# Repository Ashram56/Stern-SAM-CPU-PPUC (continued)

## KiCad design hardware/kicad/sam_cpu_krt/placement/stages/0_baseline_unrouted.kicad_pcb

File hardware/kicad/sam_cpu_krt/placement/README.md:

# SAM CPU PPUC: optimized placement, then KRT routing (run C)

The placement plan applied to the KiCadRoutingTools experiment: measure the baseline, write placement constraints,
generate placement candidates scored on ratsnest length and crossings, keep the best two, route them on a copper-free
copy with KRT, pour the zones, and grade with the JLCPCB 4-layer rules. `../` (run A) is left as it was.

`sam_cpu.kicad_pcb` here is the result: the widened candidate, routed and with zones refilled.

Red F.Cu, blue B.Cu, green In1.Cu, yellow In2.Cu; pours hidden.

## Result

Graded by `kicad-cli pcb drc --refill-zones` (KiCad 10.0.6) with `sam_cpu.kicad_dru` (copied from
`/mnt/project-files/hardware/jlcpcb_rules/`) and the JLCPCB board minimums in `sam_cpu.kicad_pro`.

| | Freerouting (0ca768b) | KRT run A (`../`) | **KRT run C (this folder)** |
|---|---|---|---|
| Placement | as drawn | as drawn | widened board, optimized |
| Unconnected items | 37 | 6 | **2**: `GI_PWM` and the Pi's two 3V3 pins (see below) |
| Clearance / short / crossing | 0 | 0 | 0 |
| Hole to hole, different nets (JLC 0.5 mm) | 5 | 0 | 0 |
| Copper to edge (JLC 0.3 mm) | 0 | 0 | 0 |
| Starved thermal reliefs | — | 21 | 15 |
| Dangling track / via stubs | — | 7 | 6 tracks, 0 vias |
| Signal track at 0.1 mm | — | 2693 mm | **0** (`--escalation off`) |
| Tracks / vias | — | 7298 / 1282 | 6033 / 1147 |
| Track length F / In1 / In2 / B (mm) | — | 7907 / 2025 / 1912 / 6796 | 8005 / 1522 / 1479 / 6150 |
| Non-isolated copper in the GND_ISO area | — | none | none |

The remaining DRC items (199 silk overlap, 120 silk over copper, 199 library, 5 silk to edge, 4 mounting holes over
6.3 mm, 4 PTH rings) are the same as on the other boards and are not routing issues. Report: `drc/drc_widened_final.rpt`.

Still open:

- `GI_PWM` (U4 to the R185 area near U15): the end at (97.8, 119.95) is boxed in by neighbouring tracks. Three passes,
  including one allowed to rip the blocking nets, did not close it. It is one short track to add by hand.
- `PI_3V3`: the Pi header's two 3V3 pins (1 and 17). The schematic had them on a no-connect flag; they are now a
  named net (`PI_3V3` label plus a PWR_FLAG, since the Pi drives it) and need one short track between the two pins.

Power tracks still under their class width (requested width not reached in a tight spot; no track went below 0.2 mm):
`Net-(JP1-B)` 26.6 mm at 0.2 instead of 0.8, `Net-(D1-A1)` 12.7 mm at 0.2 instead of 0.8, `+12V` 3.6 mm at 0.4,
`+5V` 5.2 mm at 0.2, `+3V3` 35.8 mm and `+1V1` 12.4 mm at 0.2 instead of 0.25. The JP1-B and D1-A1 sections should
be widened by hand (`scripts/power_widths.py`).

## Placement metrics

Ratsnest = sum of per-net minimum spanning trees over pad centres, without GND, +3V3 and GND_ISO (planes);
crossings = ratsnest segments crossing each other (`scripts/ratsnest.py`).

| Candidate | Ratsnest (mm) | Crossings | Notes |
|---|---|---|---|
| baseline (Freerouting 0ca768b placement) | 14534 | 3391 | |
| c1: U6/U7 swap with their caps | 14514 | 3438 | 1 courtyard overlap, dropped |
| c2: optimizer, 3 mm max move | 14052 | 2389 | |
| c3: swap + 3 mm | 14007 | 2482 | |
| c4k: swap + 6 mm, decap groups, heatsink keep-out | 13642 | 1928 | routed: 286/304 first pass |
| **c5k: widened board + swap + 10 mm, decap groups, heatsink keep-out** | **13391** | **1391** | routed: 297/304 first pass |

Both kept candidates have no courtyard or clearance overlaps, nothing in the heatsink area (x 89-137, y 71-84) and no tall
parts under the Pi. The optimizer scatters and rotates passives more than a hand layout would
(`placement_before_after.png`, baseline left, widened right); a tidy-up pass for assembly and silkscreen is still needed.

**The widened board.** The top-right part of the board was extended by 21.35 mm to x 172 (KiCad coordinates), from the
top edge down to y 126.5, where a notch keeps the Pi's overhang free. The right-edge connectors J17, J22, J23, J24 and
J30 moved right with the edge by 21.35 mm; no mounting hole moved. Check that the harness reaches the new connector
positions before keeping this.

Locked parts (`locks.txt`, `placement_constraints.yaml`): all connectors, mounting holes, SW1-3, BT1, JP1, U23/U24
(heatsink), the isolated RS485 parts and U4 with its regulator parts.

## Routing

The original-size candidate ended with 8 nets open after its clean-up pass, so only the widened one was finished.

1. `scripts/route_chain.sh`: refill zones, fan out U4 with `qfn_fanout.py`, route the isolated nets, add a keep-out
   on User.2 around GND_ISO (outline + 2 mm), then route everything else. Layer costs 1/3/3/1, grid 0.1 mm,
   `--escalation off` (no narrowing), `--hole-to-hole-clearance 0.5`. Widened board: 79 min.
2. `scripts/route_cleanup.sh`: open nets plus GND at 0.05 mm grid (13 min), then the last two nets (3 min).
3. GND pad taps: the outer GND pours were removed from a copy, GND routed so every GND pad gets its own via into the
   In1 plane, and the pours put back. This closed the last 20 GND pads the pours did not reach.
4. `kicad-cli pcb drc --refill-zones --save-board` with the JLC rules.

Stage files: `stages/0_baseline_unrouted.kicad_pcb` (copper stripped), `stages/1_placed_widened.kicad_pcb` and
`stages/1_placed_original_size.kicad_pcb` (optimized, unrouted). Placement commands (KRT `py_placer/place_optimize.py`):

```
place_optimize.py c5_wide.kicad_pcb c5k.kicad_pcb --max-displacement 10 --ignore-nets GND +3V3 GND_ISO \
  --lock $(cat locks.txt) --group-by decap --intent intent.json
```

`c5_wide` is the baseline with U6/U7 swapped (`scripts/move.py`), the outline and zones widened (`scripts/widen.py`)
and the right-edge connectors moved. `c4k` uses `--max-displacement 6` on the original outline.

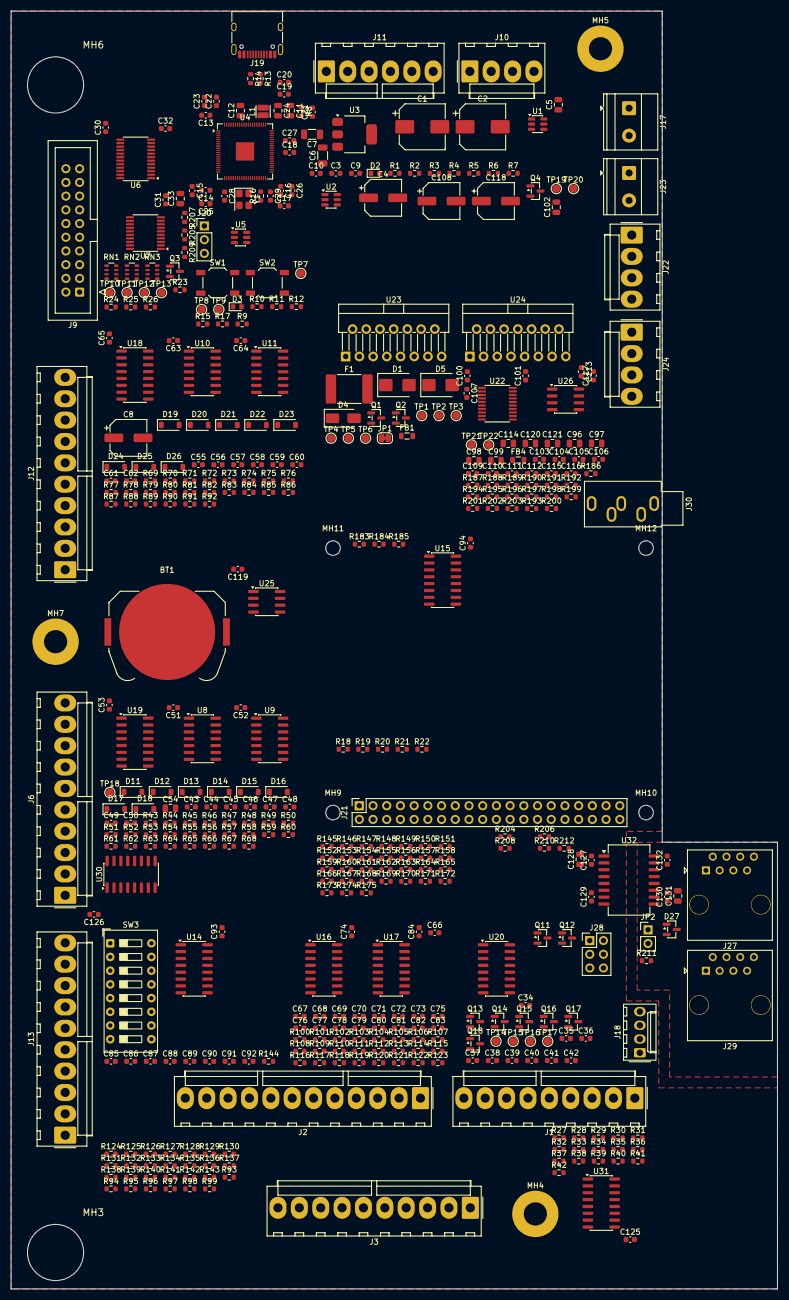
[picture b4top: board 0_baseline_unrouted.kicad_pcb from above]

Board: 4 copper layers, 142.0 x 236.8 mm, 459 parts (0 on the bottom side), 309 nets, no tracks yet.

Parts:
BT1: CR2032; BatteryHolder_Keystone_3034_1x20mm
C1, C2: 100u; CP_Elec_8x10
C3, C9, C10, C13, C14, C15, C16, C17, C18, C19, C20, C21, C22, C23, C25, C26, C27, C30, C31, C32, C34, C35, C36, C37, C38, C39, C40, C41, C42, C43, C44, C45, C46, C47, C48, C49, C50, C51, C52, C53, C55, C56, C57, C58, C59, C60, C61, C62, C63, C64, C65, C74, C84, C93, C94, C100, C101, C107, C111, C113, C117, C119, C125, C126, C127, C129, C130, C132: 100n; C_0603_1608Metric
C4, C8: 100u; CP_Elec_6.3x7.7
C5, C33, C99, C102, C114, C120, C121, C128, C131: 10u; C_0805_2012Metric
C6, C7: 10u; C_1206_3216Metric
C11, C12, C24: 4.7u; C_0805_2012Metric
C28, C29: 15p; C_0603_1608Metric
C54: 22u; C_0805_2012Metric
C66, C67, C68, C69, C70, C71, C72, C73, C75, C76, C77, C78, C79, C80, C81, C82, C83, C85, C86, C87, C88, C89, C90, C91, C92: 47p; C_0603_1608Metric
C96, C97, C98: 2.2u; C_0805_2012Metric
C103, C105: 2.2n; C_0603_1608Metric
C104, C106, C109, C110, C115, C116: 1u; C_0603_1608Metric
C108, C118: 470u; CP_Elec_6.3x7.7
C112: 220n; C_0603_1608Metric
D1: SMBJ5.0CA; D_SMB
D2: green; LED_0603_1608Metric
D3: yellow; LED_0603_1608Metric
D4: S1M; D_SMA
D5: SMBJ15A; D_SMB
D11, D12, D13, D14, D15, D16, D17, D18, D19, D20, D21, D22, D23, D24, D25, D26: 1N4148W; D_SOD-123
D27: SM712; SOT-23
F1: 4A hold; Fuse_2920_7451Metric
FB1: 3A; L_0805_2012Metric
FB4: FB; L_0805_2012Metric
J1: J1 SWITCH COLUMNS; Molex_KK-396_A-41791-0009_1x09_P3.96mm_Vertical
J2: J2 DEDICATED; Molex_KK-396_A-41791-0012_1x12_P3.96mm_Vertical
J3: J3 DEDICATED; Molex_KK-396_A-41791-0010_1x10_P3.96mm_Vertical
J6: J6 SWITCH ROWS; Molex_KK-396_A-41791-0010_1x10_P3.96mm_Vertical
J9: J9 IO BUS; IDC-Header_2x10_P2.54mm_Vertical
J10: J10 SPEAKERS; Molex_KK-396_A-41791-0004_1x04_P3.96mm_Vertical
J11: J11 POWER; Molex_KK-396_A-41791-0006_1x06_P3.96mm_Vertical
J12: J12 SWITCH ROWS; Molex_KK-396_A-41791-0010_1x10_P3.96mm_Vertical
J13: J13 DEDICATED; Molex_KK-396_A-41791-0010_1x10_P3.96mm_Vertical
J17: EXT 5V; TerminalBlock_Phoenix_MKDS-1,5-2-5.08_1x02_P5.08mm_Horizont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
J18: J18 GI DIMMER; Molex_KK-254_AE-6410-04A_1x04_P2.54mm_Vertical
J19: USB-C (to Pi); USB_C_Receptacle_HRO_TYPE-C-31-M-12
J20: SWD; PinHeader_1x03_P2.54mm_Vertical
J21: Raspberry Pi 40-pin; PinSocket_2x20_P2.54mm_Vertical
J22: J22 STEREO; Molex_KK-396_A-41791-0004_1x04_P3.96mm_Vertical
J23: EXT 12V; TerminalBlock_Phoenix_MKDS-1,5-2-5.08_1x02_P5.08mm_Horizont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
J24: J24 SUBWOOFER; Molex_KK-396_A-41791-0004_1x04_P3.96mm_Vertical
J27: J27 RS485 IN; RJ45_OST_PJ012-8P8CX_Vertical
J28: J28 I2S IN; PinHeader_2x03_P2.54mm_Vertical
J29: J29 RS485 OUT; RJ45_OST_PJ012-8P8CX_Vertical
J30: J30 LINE IN; Jack_3.5mm_CUI_SJ1-3535NG_Horizontal
JP1: J11 5V; SolderJumper-2_P1.3mm_Bridged_RoundedPad1.0x1.5mm
JP2: TERM; PinHeader_1x02_P2.54mm_Vertical
L1: 3.3u; L_Cenker_CKCS201610
MH3, MH6: Keyhole; Keyhole_SAM
MH4, MH5, MH7: MountingHole_4.3mm_M4_Pad
MH9, MH10, MH11, MH12: MountingHole_2.7mm_M2.5
Q1, Q2: AO3401A; SOT-23
Q3, Q4: 2N7002; SOT-23
Q11, Q12, Q13, Q14, Q15, Q16, Q17, Q18: MMBT3904; SOT-23
R1, R2, R10, R185, R195, R203: 100k; R_0603_1608Metric
R3, R15, R16, R17, R20, R21, R27, R28, R29, R30, R31, R32, R33, R34, R35, R36, R37, R38, R39, R40, R41, R42, R43, R46, R49, R52, R55, R58, R61, R64, R69, R72, R75, R78, R81, R84, R87, R90, R204, R205, R206, R207, R208, R209: 1k; R_0603_1608Metric
R4, R5, R7, R9, R22, R23, R24, R26, R45, R48, R51, R54, R57, R60, R63, R66, R71, R74, R77, R80, R83, R86, R89, R92, R168, R169, R170, R171, R172, R173, R174, R175, R186, R196, R197, R198, R201, R202, R210, R212: 10k; R_0603_1608Metric
R6: 33k; R_0603_1608Metric
R8, R18, R19, R25: 33; R_0603_1608Metric
R11, R12: 5.1k; R_0603_1608Metric
R13, R14: 27; R_0603_1608Metric
R44, R47, R50, R53, R56, R59, R62, R65, R70, R73, R76, R79, R82, R85, R88, R91: 220; R_0603_1608Metric
R67, R68: 3.3k; R_0603_1608Metric
R93, R96, R99, R102, R105, R108, R111, R114, R120, R123, R126, R129, R132, R135, R138, R141, R144, R147, R150, R153, R156, R159, R162, R165: 1.5k; R_0603_1608Metric
R94, R97, R100, R103, R106, R109, R112, R115, R118, R121, R124, R127, R130, R133, R136, R139, R142, R145, R148, R151, R154, R157, R160, R163, R166: 39k; R_0603_1608Metric
R95, R98, R101, R104, R107, R110, R113, R116, R119, R122, R125, R128, R131, R134, R137, R140, R143, R146, R149, R152, R155, R158, R161, R164, R167: 68k; R_0603_1608Metric
R117: 4.7k; R_0603_1608Metric
R183, R184: 100; R_0603_1608Metric
R187, R190: 470; R_0603_1608Metric
R188, R191, R199: 22k; R_0603_1608Metric
R189, R192, R200: 1.8k; R_0603_1608Metric
R193, R194: 20k; R_0603_1608Metric
R211: 120; R_0603_1608Metric
RN1, RN2, RN3: 33; R_Array_Convex_4x0603
SW1: RESET; SW_SPST_TL3342
SW2: BOOTSEL; SW_SPST_TL3342
SW3: DIP x8; SW_DIP_SPSTx08_Slide_9.78x22.5mm_W7.62mm_P2.54mm
TP1: +5V; TestPoint_Pad_D1.5mm
TP2: +3V3; TestPoint_Pad_D1.5mm
TP3: +4V5; TestPoint_Pad_D1.5mm
TP4: +12V; TestPoint_Pad_D1.5mm
TP5, TP6, TP9, TP22: GND; TestPoint_Pad_D1.5mm
TP7: +1V1; TestPoint_Pad_D1.5mm
TP8: RUN; TestPoint_Pad_D1.5mm
TP10: J9_IOSTB; TestPoint_Pad_D1.5mm
TP11: J9_NBRESET; TestPoint_Pad_D1.5mm
TP12: J9_D0; TestPoint_Pad_D1.5mm
TP13: J9_A0; TestPoint_Pad_D1.5mm
TP14: STB1; TestPoint_Pad_D1.5mm
TP15: STB2; TestPoint_Pad_D1.5mm
TP16: SW_CLK; TestPoint_Pad_D1.5mm
TP17: SW_DATA; TestPoint_Pad_D1.5mm
TP18: VREF; TestPoint_Pad_D1.5mm
TP19: DAC_OUTL; TestPoint_Pad_D1.5mm
TP20: DAC_OUTR; TestPoint_Pad_D1.5mm
TP21: SUB_OUT; TestPoint_Pad_D1.5mm
U1, U2: LTC4412; TSOT-23-6
U3: NCP1117-3.3; SOT-223-3_TabPin2
U4: RP2354B; QFN-80-1EP_10x10mm_P0.4mm_EP3.4x3.4mm
U5: TPS3808G33; SOT-23-6
U6: SN74LVC8T245; TSSOP-24_4.4x7.8mm_P0.65mm
U7: 74AHCT541; TSSOP-20_4.4x6.5mm_P0.65mm
U8, U9, U10, U11: LM339; SOIC-14_3.9x8.7mm_P1.27mm
U14, U15, U16, U17, U18, U19, U30: 74HC165; SOIC-16_3.9x9.9mm_P1.27mm
U20, U31: 74HC595; SOIC-16_3.9x9.9mm_P1.27mm
U22: PCM5102A; TSSOP-20_4.4x6.5mm_P0.65mm
U23, U24: TDA7297; TO-220-15_P2.54x5.08mm_StaggerOdd_Lead4.58mm_Vertical
U25: DS3231MZ; SOIC-8_3.9x4.9mm_P1.27mm
U26: OPA1678; SOIC-8_3.9x4.9mm_P1.27mm
U32: ADM2682E; SOIC-16W_7.5x12.8mm_P1.27mm
Y1: 12MHz; Crystal_SMD_3225-4Pin_3.2x2.5mm

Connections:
+1V1: C24.1, C25.1, C26.1, C27.1, L1.2, TP7.1, U4.10, U4.32, U4.51, U4.65
+3V3: C7.1, C12.1, C13.1, C14.1, C15.1, C16.1, C17.1, C18.1, C19.1, C20.1, C21.1, C22.1, C23.1, C30.1, C34.1, C53.1, C65.1, C74.1, C84.1, C93.1, C94.1, C100.1, C101.1, C102.1, C119.1, C125.1, C126.1, C127.1, C128.1, C129.1, FB4.1, R3.1, R8.1, R9.1, R22.1, R23.1, R26.1, R45.1, R48.1, R51.1, R54.1, R57.1, R60.1, R63.1, R66.1, R71.1, R74.1, R77.1, R80.1, R83.1, R86.1, R89.1, R92.1, R168.1, R169.1, R170.1, R171.1, R172.1, R173.1, R174.1, R175.1, R186.1, R212.1, TP2.1, U3.2, U4.5, U4.15, U4.24, U4.29, U4.41, U4.50, U4.59, U4.60, U4.64, U4.68, U4.69, U4.76, U5.5, U5.6, U6.1, U14.16, U15.16, U16.16, U17.16, U18.16, U19.16, U20.10, U20.16, U22.1, U22.20, U25.2, U30.16, U31.10, U31.16, U32.2, U32.7
+4V5: C8.1, C51.1, C52.1, C63.1, C64.1, D4.1, R28.1, R30.1, R32.1, R34.1, R36.1, R38.1, R40.1, R42.1, R43.1, R46.1, R49.1, R52.1, R55.1, R58.1, R61.1, R64.1, R67.1, R69.1, R72.1, R75.1, R78.1, R81.1, R84.1, R87.1, R90.1, R93.1, R96.1, R99.1, R102.1, R105.1, R108.1, R111.1, R114.1, R117.1, R120.1, R123.1, R126.1, R129.1, R132.1, R135.1, R138.1, R141.1, R144.1, R147.1, R150.1, R153.1, R156.1, R159.1, R162.1, R165.1, TP3.1, U8.3, U9.3, U10.3, U11.3
+5V: C4.1, C5.1, C6.1, C31.1, C32.1, C33.1, D4.2, J18.1, J21.2, J21.4, Q1.2, Q2.2, R4.1, R201.1, R202.1, TP1.1, U1.6, U2.6, U3.3, U6.23, U6.24, U7.20
+12V: C2.1, C3.1, C107.1, C108.1, C113.1, C117.1, C118.1, D5.1, F1.2, R6.1, R197.1, TP4.1, U23.3, U23.13, U24.3, U24.13, U26.8
/Audio/AFL: C103.1, C109.1, R187.2, R188.1
/Audio/AFR: C105.1, C110.1, R190.2, R191.1
/Audio/AMP_PLAY: C121.1, Q4.3, R202.2, U23.6, U24.6
/Audio/AMP_STBY: C120.1, R201.2, U23.7, U24.7
/Audio/SUB_OUT: C112.2, C115.1, TP21.1, U26.1, U26.2
/IO bus/BA0: RN3.5, U7.14
/IO bus/BA1: RN3.6, U7.15
/IO bus/BA3: RN3.8, U7.17
/IO bus/BD0: RN1.5, U6.14
/IO bus/BD1: RN1.6, U6.15
/IO bus/BD2: RN1.7, U6.16
/IO bus/BD3: RN1.8, U6.17
/IO bus/BD4: RN2.5, U6.18
/IO bus/BD5: RN2.6, U6.19
/IO bus/BD6: RN2.7, U6.20
/IO bus/BD7: RN2.8, U6.21
/IO bus/BSTB: R25.1, U7.18
/MCU and Pi/BOOTSEL: R15.2, R21.2, U4.75
/MCU and Pi/MR_N: R20.2, SW1.1, U5.3
/MCU and Pi/PI_SCL: J21.5, U25.8
/MCU and Pi/PI_SDA: J21.3, U25.7
/MCU and Pi/SWCLK: J20.1, J21.18, U4.33
/MCU and Pi/SWDIO: J20.3, J21.22, U4.34
AMP_MUTE: Q4.1, R203.1, U4.48
AUD_AMP_L: J30.T, R187.1
AUD_AMP_R: J30.R, R190.1
AUD_DAC_L: J30.TN, TP19.1, U22.6
AUD_DAC_R: J30.RN, TP20.1, U22.7
BUS_A0: U4.6, U7.6
BUS_A1: U4.7, U7.5
BUS_A2: U4.8, U7.4
BUS_A3: U4.9, U7.3
BUS_D0: U4.77, U6.10
BUS_D1: U4.78, U6.9
BUS_D2: U4.79, U6.8
BUS_D3: U4.80, U6.7
BUS_D4: U4.1, U6.6
BUS_D5: U4.2, U6.5
BUS_D6: U4.3, U6.4
BUS_D7: U4.4, U6.3
BUS_DIR: R24.1, U4.12, U6.2
BUS_IOSTB: U4.11, U7.2
BUS_OE_N: R23.2, U4.14, U6.22, U7.1, U7.19
CHAIN2: U15.9, U16.10
CHAIN4: U17.9, U18.10
CHAIN5: U18.9, U19.10
CHAIN6: U19.9, U30.10
FRAME_CS_N: J21.24, U4.52
FRAME_MOSI: J21.19, U4.49
FRAME_SCK: J21.23, U4.53
GI_PWM: R183.1, R185.1, U4.47
GI_SPARE: R184.1, U31.1
GND: BT1.2, C1.2, C2.2, C3.2, C4.2, C5.2, C6.2, C7.2, C8.2, C9.2, C10.2, C11.2, C12.2, C13.2, C14.2, C15.2, C16.2, C17.2, C18.2, C19.2, C20.2, C21.2, C22.2, C23.2, C24.2, C25.2, C26.2, C27.2, C28.2, C29.2, C30.2, C31.2, C32.2, C33.2, C34.2, C35.2, C36.2, C37.2, C38.2, C39.2, C40.2, C41.2, C42.2, C43.2, C44.2, C45.2, C46.2, C47.2, C48.2, C49.2, C50.2, C51.2, C52.2, C53.2, C54.2, C55.2, C56.2, C57.2, C58.2, C59.2, C60.2, C61.2, C62.2, C63.2, C64.2, C65.2, C66.2, C67.2, C68.2, C69.2, C70.2, C71.2, C72.2, C73.2, C74.2, C75.2, C76.2, C77.2, C78.2, C79.2, C80.2, C81.2, C82.2, C83.2, C84.2, C85.2, C86.2, C87.2, C88.2, C89.2, C90.2, C91.2, C92.2, C93.2, C94.2, C97.2, C98.2, C99.2, C100.2, C101.2, C102.2, C103.2, C105.2, C107.2, C108.2, C111.2, C113.2, C114.2, C117.2, C118.2, C119.2, C120.2, C121.2, C125.2, C126.2, C127.2, C128.2, C129.2, D1.2, D2.1, D3.1, D5.2, J2.11, J2.12, J3.10, J6.10, J9.19, J9.20, J11.2, J11.4, J11.5, J12.10, J13.10, J17.2, J18.2, J19.A1, J19.A12, J19.B1, J19.B12, J19.SH, J20.2, J21.6, J21.9, J21.14, J21.20, J21.25, J21.30, J21.34, J21.39, J23.2, J28.2, J28.4, J28.6, J30.S, Q3.2, Q4.2, Q11.2, Q12.2, Q13.2, Q14.2, Q15.2, Q16.2, Q17.2, Q18.2, R2.2, R5.2, R7.2, R10.2, R11.2, R12.2, R24.2, R68.2, R95.2, R98.2, R101.2, R104.2, R107.2, R110.2, R113.2, R116.2, R119.2, R122.2, R125.2, R128.2, R131.2, R134.2, R137.2, R140.2, R143.2, R146.2, R149.2, R152.2, R155.2, R158.2, R161.2, R164.2, R167.2, R185.2, R189.2, R192.2, R198.2, R200.2, R203.2, R210.2, SW1.2, SW2.2, SW3.9, SW3.10, SW3.11, SW3.12, SW3.13, SW3.14, SW3.15, SW3.16, TP5.1, TP6.1, TP9.1, TP22.1, U1.2, U1.3, U2.2, U3.1, U4.62, U4.81, U5.2, U6.11, U6.12, U6.13, U7.7, U7.8, U7.9, U7.10, U8.12, U9.12, U10.12, U11.12, U14.8, U14.10, U14.15, U15.8, U15.15, U16.8, U16.15, U17.8, U17.15, U18.8, U18.15, U19.8, U19.15, U20.8, U20.13, U22.3, U22.9, U22.10, U22.11, U22.12, U22.16, U22.19, U23.8, U23.9, U24.8, U24.9, U25.5, U26.4, U30.3, U30.4, U30.5, U30.6, U30.8, U30.12, U30.13, U30.14, U30.15, U31.8, U31.13, U32.1, U32.8, Y1.2, Y1.4
GND_ISO: C130.2, C131.2, C132.2, D27.3, J27.7, J27.8, J29.7, J29.8, U32.9, U32.16
I2S_BCK: J21.12, J28.1, U22.13
I2S_DIN: J21.40, J28.5, U22.14
I2S_LRCK: J21.35, J28.3, U22.15
LED_STATUS: R17.2, U31.15
MEM_PROTECT: C75.1, R118.2, R119.1, U30.11
NBRESET_DRV: Q3.1, R26.2, U4.13
unnamed: BT1.1, U25.6
unnamed: C29.1, R16.1, Y1.3
unnamed: C104.1, R188.2, R189.1
unnamed: C106.1, R191.2, R192.1
unnamed: C109.2, R193.1
unnamed: C110.2, R194.1
unnamed: C112.1, R193.2, R194.2, R195.1, R196.1
unnamed: C115.2, R199.1
unnamed: C116.1, R199.2, R200.1
unnamed: C1.1, D1.1, J17.1, Q1.3, R1.1, U1.1
unnamed: D2.2, R3.2
unnamed: D3.2, R17.1
unnamed: D11.2, R43.2, R44.1
unnamed: D11.1, J6.1
unnamed: D12.2, R46.2, R47.1
unnamed: D12.1, J6.2
unnamed: D13.2, R49.2, R50.1
unnamed: D13.1, J6.3
unnamed: D14.2, R52.2, R53.1
unnamed: D14.1, J6.5
unnamed: D15.2, R55.2, R56.1
unnamed: D15.1, J6.6
unnamed: D16.2, R58.2, R59.1
unnamed: D16.1, J6.7
unnamed: D17.2, R61.2, R62.1
unnamed: D17.1, J6.8
unnamed: D18.2, R64.2, R65.1
unnamed: D18.1, J6.9
unnamed: D19.2, R69.2, R70.1
unnamed: D19.1, J12.1
unnamed: D20.2, R72.2, R73.1
unnamed: D20.1, J12.2
unnamed: D21.2, R75.2, R76.1
unnamed: D21.1, J12.3
unnamed: D22.2, R78.2, R79.1
unnamed: D22.1, J12.4
unnamed: D23.2, R81.2, R82.1
unnamed: D23.1, J12.6
unnamed: D24.2, R84.2, R85.1
unnamed: D24.1, J12.7
unnamed: D25.2, R87.2, R88.1
unnamed: D25.1, J12.8
unnamed: D26.2, R90.2, R91.1
unnamed: D26.1, J12.9
unnamed: D27.1, J27.1, J29.1, R211.1, U32.11, U32.14
unnamed: D27.2, J27.2, J29.2, JP2.2, U32.12, U32.13
unnamed: C35.1, J1.1, Q11.3, R28.2, TP14.1
unnamed: C36.1, J1.3, Q12.3, R30.2, TP15.1
unnamed: C37.1, J1.4, Q13.3, R32.2
unnamed: C38.1, J1.5, Q14.3, R34.2
unnamed: C39.1, J1.6, Q15.3, R36.2
unnamed: C40.1, J1.7, Q16.3, R38.2
unnamed: C41.1, J1.8, Q17.3, R40.2
unnamed: C42.1, J1.9, Q18.3, R42.2
unnamed: J2.1, R93.2, R94.1
unnamed: J2.2, R96.2, R97.1
unnamed: J2.3, R99.2, R100.1
unnamed: J2.4, R102.2, R103.1
unnamed: J2.6, R105.2, R106.1
unnamed: J2.7, R108.2, R109.1
unnamed: J2.8, R111.2, R112.1
unnamed: J2.9, R114.2, R115.1
unnamed: J2.10, R117.2, R118.1
unnamed: J3.1, R120.2, R121.1
unnamed: J3.2, R123.2, R124.1
unnamed: J3.4, R126.2, R127.1
unnamed: J3.5, R129.2, R130.1
unnamed: J3.6, R132.2, R133.1
unnamed: J3.7, R135.2, R136.1
unnamed: J3.8, R138.2, R139.1
unnamed: J3.9, R141.2, R142.1
unnamed: J9.1, RN1.1
unnamed: J9.2, RN2.4
unnamed: J9.3, RN1.2
unnamed: J9.4, RN2.3
unnamed: J9.5, RN1.3
unnamed: J9.6, RN2.2
unnamed: J9.7, RN1.4, TP12.1
unnamed: J9.8, RN2.1
unnamed: J9.12, RN3.4, TP13.1
unnamed: J9.13, Q3.3, TP11.1
unnamed: J9.14, RN3.3
unnamed: J9.15, R25.2, TP10.1
unnamed: J9.16, RN3.2
unnamed: J9.18, RN3.1
unnamed: J10.1, J22.1, U23.1
unnamed: J10.2, J22.3, U23.15
unnamed: J10.3, J22.2, U23.2
unnamed: J10.4, J22.4, U23.14
unnamed: FB1.1, J11.1
unnamed: J13.1, R144.2, R145.1
unnamed: J13.3, R147.2, R148.1
unnamed: J13.4, R150.2, R151.1
unnamed: J13.5, R153.2, R154.1
unnamed: J13.6, R156.2, R157.1
unnamed: J13.7, R159.2, R160.1
unnamed: J13.8, R162.2, R163.1
unnamed: J13.9, R165.2, R166.1
unnamed: J18.3, R183.2
unnamed: J18.4, R184.2
unnamed: J19.A5, R11.1
unnamed: J19.B5, R12.1
unnamed: J19.A6, J19.B6, R14.1
unnamed: J19.A7, J19.B7, R13.1
unnamed: J19.A4, J19.A9, J19.B4, J19.B9, R10.1
unnamed: J21.8, R18.1
unnamed: J21.10, R19.1
unnamed: J21.15, R20.1
unnamed: J21.13, R21.1
unnamed: F1.1, J23.1
unnamed: J24.1, U24.1
unnamed: J24.2, U24.2
unnamed: J24.3, U24.15
unnamed: J24.4, U24.14
unnamed: FB1.2, JP1.1
unnamed: JP1.2, Q2.3, U2.1
unnamed: JP2.1, R211.2
unnamed: Q1.1, U1.5
unnamed: Q2.1, U2.5
unnamed: Q11.1, R27.2
unnamed: Q12.1, R29.2
unnamed: Q13.1, R31.2
unnamed: Q14.1, R33.2
unnamed: Q15.1, R35.2
unnamed: Q16.1, R37.2
unnamed: Q17.1, R39.2
unnamed: Q18.1, R41.2
unnamed: R15.1, SW2.1
unnamed: RN3.7, U7.16
unnamed: R1.2, R2.1, U2.3
unnamed: R9.2, TP8.1, U4.35, U5.1
unnamed: R13.2, U4.66
unnamed: R14.2, U4.67
unnamed: C11.1, R8.2, U4.61
unnamed: L1.1, U4.63
unnamed: C28.1, U4.30, Y1.1
unnamed: R16.2, U4.31
unnamed: C43.1, R44.2, U8.5
unnamed: C44.1, R47.2, U8.7
unnamed: C45.1, R50.2, U8.11
unnamed: C46.1, R53.2, U8.9
unnamed: C47.1, R56.2, U9.5
unnamed: C48.1, R59.2, U9.7
unnamed: C49.1, R62.2, U9.11
unnamed: C50.1, R65.2, U9.9
unnamed: C55.1, R70.2, U10.5
unnamed: C56.1, R73.2, U10.7
unnamed: C57.1, R76.2, U10.11
unnamed: C58.1, R79.2, U10.9
unnamed: C59.1, R82.2, U11.5
unnamed: C60.1, R85.2, U11.7
unnamed: C61.1, R88.2, U11.11
unnamed: C62.1, R91.2, U11.9
unnamed: R168.2, SW3.1, U14.11
unnamed: R169.2, SW3.2, U14.12
unnamed: R170.2, SW3.3, U14.13
unnamed: R171.2, SW3.4, U14.14
unnamed: R172.2, SW3.5, U14.3
unnamed: R173.2, SW3.6, U14.4
unnamed: R174.2, SW3.7, U14.5
unnamed: R175.2, SW3.8, U14.6
unnamed: U14.9, U15.10
unnamed: C85.1, R145.2, R146.1, U15.11
unnamed: C86.1, R148.2, R149.1, U15.12
unnamed: C87.1, R151.2, R152.1, U15.13
unnamed: C88.1, R154.2, R155.1, U15.14
unnamed: C89.1, R157.2, R158.1, U15.3
unnamed: C90.1, R160.2, R161.1, U15.4
unnamed: C91.1, R163.2, R164.1, U15.5
unnamed: C92.1, R166.2, R167.1, U15.6
unnamed: C76.1, R121.2, R122.1, U16.11
unnamed: C77.1, R124.2, R125.1, U16.12
unnamed: C78.1, R127.2, R128.1, U16.13
unnamed: C79.1, R130.2, R131.1, U16.14
unnamed: C80.1, R133.2, R134.1, U16.3
unnamed: C81.1, R136.2, R137.1, U16.4
unnamed: C82.1, R139.2, R140.1, U16.5
unnamed: C83.1, R142.2, R143.1, U16.6
unnamed: U16.9, U17.10
unnamed: C66.1, R94.2, R95.1, U17.11
unnamed: C67.1, R97.2, R98.1, U17.12
unnamed: C68.1, R100.2, R101.1, U17.13
unnamed: C69.1, R103.2, R104.1, U17.14
unnamed: C70.1, R106.2, R107.1, U17.3
unnamed: C71.1, R109.2, R110.1, U17.4
unnamed: C72.1, R112.2, R113.1, U17.5
unnamed: C73.1, R115.2, R116.1, U17.6
unnamed: R71.2, U10.2, U18.11
unnamed: R74.2, U10.1, U18.12
unnamed: R77.2, U10.13, U18.13
unnamed: R80.2, U10.14, U18.14
unnamed: R83.2, U11.2, U18.3
unnamed: R86.2, U11.1, U18.4
unnamed: R89.2, U11.13, U18.5
unnamed: R92.2, U11.14, U18.6
unnamed: R45.2, U8.2, U19.11
unnamed: R48.2, U8.1, U19.12
unnamed: R51.2, U8.13, U19.13
unnamed: R54.2, U8.14, U19.14
unnamed: R57.2, U9.2, U19.3
unnamed: R60.2, U9.1, U19.4
unnamed: R63.2, U9.13, U19.5
unnamed: R66.2, U9.14, U19.6
unnamed: R27.1, U20.15
unnamed: R29.1, U20.1
unnamed: R31.1, U20.2
unnamed: R33.1, U20.3
unnamed: R35.1, U20.4
unnamed: R37.1, U20.5
unnamed: R39.1, U20.6
unnamed: R41.1, U20.7
unnamed: C99.1, FB4.2, U22.8
unnamed: C96.2, U22.4
unnamed: C96.1, U22.2
unnamed: C97.1, U22.18
unnamed: C98.1, U22.5
unnamed: R186.2, U22.17
unnamed: C104.2, U23.4
unnamed: C106.2, U23.12
unnamed: C116.2, U24.4, U24.12
unnamed: C111.1, R196.2, U26.3
unnamed: C114.1, R195.2, R197.2, R198.1, U26.5
unnamed: U26.6, U26.7
unnamed: R208.2, R209.2, R210.1, U32.4, U32.5
unnamed: R204.2, R205.2, R212.2, U32.3
unnamed: R206.2, R207.2, U32.6
unnamed: C130.1, C131.1, C132.1, U32.10, U32.15
PI_RS485_DE: J21.26, R208.1
PI_RS485_RX: J21.29, R204.1
PI_RS485_TX: J21.7, R206.1
RP_IRQ_N: J21.16, R22.2, U4.46
RP_RS485_DE: R209.1, U4.22
RP_RS485_RX: R205.1, U4.21
RP_RS485_TX: R207.1, U4.20
RP_UART_RX: R18.2, U4.56
RP_UART_TX: R19.2, U4.55
STB_CHAIN: U20.14, U31.9
STB_DATA: U4.19, U31.14
SW_CLK: TP16.1, U4.16, U14.2, U15.2, U16.2, U17.2, U18.2, U19.2, U20.11, U30.2, U31.11
SW_DATA: TP17.1, U4.18, U30.9
SW_LOAD_N: U4.17, U14.1, U15.1, U16.1, U17.1, U18.1, U19.1, U20.12, U30.1, U31.12
VMON_5V: C9.1, R4.2, R5.1, U4.57
VMON_12V: C10.1, R6.2, R7.1, U4.58
VREF: C54.1, R67.2, R68.1, TP18.1, U8.4, U8.6, U8.8, U8.10, U9.4, U9.6, U9.8, U9.10, U10.4, U10.6, U10.8, U10.10, U11.4, U11.6, U11.8, U11.10

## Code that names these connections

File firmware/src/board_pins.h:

// RP2354B GPIO map of the SAM CPU board.
//
// Source of truth: hardware/kicad/sam_cpu/mcu.kicad_sch (PR #4) and
// hardware/kicad/README.md "RP2354B GPIO map".
// Keep this file in step with the schematic.
//
// SPDX-License-Identifier: GPL-3.0-or-later
#pragma once

// ---- PIO0, GPIO base 0: SAM IO bus on J9 ---------------------------------
// D0-D7 then A0-A3 on consecutive pins, so one `out pins, 12` drives a whole
// address + data word.
#define PIN_BUS_D0 0          // D0-D7 = GPIO0-7
#define PIN_BUS_A0 8          // A0-A3 = GPIO8-11
#define PIN_BUS_IOSTB 12      // side-set bit 0, active low (through 74AHCT541)
#define PIN_BUS_DIR 13        // side-set bit 1, SN74LVC8T245 DIR: 1 = RP2354B drives J9
#define PIN_NBRESET_DRV 14    // high = 2N7002 on = IO board held in reset (pulled up at boot)
#define PIN_BUS_OE_N 15       // low = both J9 buffers enabled (pulled up at boot)

// ---- PIO1, GPIO base 16: switch shift chain ------------------------------
#define PIN_SW_CLK 16         // shared 74HC165 / 74HC595 shift clock (side-set bit 0)
#define PIN_SW_LOAD_N 17      // 165 parallel load (low) + 595 latch (rising edge) (side-set bit 1)
#define PIN_SW_DATA 18        // serial data in from the 165 chain (U30 QH)
#define PIN_STB_DATA 19       // serial data out to the 595 chain (U31 SER)

// GPIO20-36 were the DMD outputs (J5 and two HUB75), removed from the board:
// the Pi drives the display. The board now puts an RS485 port on GPIO20-22
// (UART1 TX, RX, DE); the firmware does not use it yet.

// ---- Misc -----------------------------------------------------------------
#define PIN_RP_IRQ_N 37       // to the Pi: low = "switch changed, poll me"
#define PIN_GI_PWM 38         // J18 GI dimmer board, PWM (slice 11 A)
#define PIN_AMP_MUTE 39       // audio amplifier mute, high = muted (pull-down on the board)

// GPIO40-42 (frame SPI from the Pi) have no use now that the DMD is gone.

#define PIN_SPARE_43 43
#define PIN_LINK_UART_TX 44   // UART0 TX (function 2 on GPIO44)
#define PIN_LINK_UART_RX 45   // UART0 RX
#define PIN_VMON_5V 46        // ADC channel 6
#define PIN_VMON_12V 47       // ADC channel 7

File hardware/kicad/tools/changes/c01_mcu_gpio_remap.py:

"""Change 01 (2026-10-06): two HD DMD panels. Re-assign RP2354B GPIOs on the MCU sheet, in place.
Pin map: /mnt/project-files/hardware/dmd_two_panel_pin_proposal.md (17-signal variant)."""
import sys, os, re
HERE = os.path.dirname(os.path.abspath(__file__))
sys.path.insert(0, HERE); sys.path.insert(0, os.path.dirname(HERE))
import schlib as L
import design2
from kigen import pin_outward

F = os.path.join(HERE, '..', '..', 'sam_cpu', 'mcu.kicad_sch')
NEW = {20: 'DMD_D0', 21: 'DMD_D1', 22: 'DMD_D2', 23: 'DMD_D3', 24: 'DMD_D4', 25: 'DMD_D5', 26: 'DMD_D6',
       27: 'DMD_D7', 28: 'DMD_D8', 29: 'DMD_D9', 30: 'DMD_D10', 31: 'DMD_D11',
       32: 'DMD_CLK', 33: 'DMD_LAT', 34: 'DMD_OE', 35: 'DMD_A', 36: 'DMD_B',
       37: 'RP_IRQ_N', 38: 'GI_PWM', 39: 'AMP_MUTE', 40: 'FRAME_MOSI', 41: 'FRAME_CS_N', 42: 'FRAME_SCK',
       44: 'RP_UART_TX', 45: 'RP_UART_RX', 46: 'VMON_5V', 47: 'VMON_12V'}

page = [p for p in design2.PAGES if p.filename == 'mcu.kicad_sch'][0]
u4 = [q for q in page.parts if q.ref == 'U4'][0]
gpio_pin = {int(p['name'].split('/')[0][4:]): p['number'] for p in u4.sd.pins if p['name'].startswith('GPIO')}


def outward(part, num):
    p = part.pin(num)
    d = pin_outward(p['angle'], part.rot)
    if part.mirror == 'y':
        d = {'L': 'R', 'R': 'L'}.get(d, d)
    return d


# every pin end on the sheet, to find what a removed wire used to connect
ends = []
for part in page.parts:
    for p in part.unit_pins():
        if part.lib_id.startswith('power:'):
            continue
        ends.append((part, p['number'], part.pin_pos(p['number'])))

text = open(F).read()
head, blocks, foot = L.split(text)
drop, add = set(), []
for g, new in sorted(NEW.items()):
    num = gpio_pin[g]
    P = u4.pin_pos(num)
    d = outward(u4, num)
    old = u4.nets[num]
    if old == new:
        continue
    nc = [i for i, b in enumerate(blocks) if L.kind(b) == 'no_connect' and L.same(L.at(b)[:2], P)]
    if nc:
        drop |= set(nc)
        L.stub_label(add, P, d, new)
        continue
    q = (P[0] + L.DV[d][0] * L.STUB, P[1] + L.DV[d][1] * L.STUB)
    lab = [i for i, b in enumerate(blocks) if L.kind(b) == 'global_label' and L.same(L.at(b)[:2], q)]
    if lab:
        i = lab[0]
        blocks[i] = blocks[i].replace('(global_label "%s"' % old, '(global_label "%s"' % new, 1)
        continue
    # routed with wires on this sheet: remove the run, label both ends
    ws, js, ls, pts = L.wire_component(blocks, P)
    assert ws, (g, old)
    drop |= ws | js | ls
    L.stub_label(add, P, d, new)
    for part, n2, e in ends:
        if part is u4 and n2 == num:
            continue
        if any(L.same(e, x) for x in pts):
            d2 = outward(part, n2)
            if part.ref == 'R17':      # keep LED_STATUS clear of the GPIO46 label on the same row
                k = (e[0] + 2.54, e[1]); m = (k[0], k[1] + 5.08)
                add += [L.wire(e, k), L.wire(k, m), L.glabel(old, m, 'D')]
            elif part.ref == 'R18':    # step up so the label clears R19 next to it
                k = (e[0], e[1] - 2.54)
                add += [L.wire(e, k), L.glabel(old, k, 'R')]
            else:
                L.stub_label(add, e, d2, old)
            print('GPIO%d: %s moved off, %s.%s keeps %s by label' % (g, old, part.ref, n2, old))
# GPIO43 becomes free; old users of 43 none. Pins left without a net get a no-connect
blocks = [b for i, b in enumerate(blocks) if i not in drop] + add
s = L.join(head, blocks, foot)
s = s.replace('PIO2 DMD on GPIO21-27, GPIO31 coin door memory protect.',
              'PIO2 drives two HD DMD panels on GPIO20-36 (data 20-31, CLK, LAT, OE, A, B); the original DMD (J5) shares GPIO20-26.'
              '\\nFrames from the Pi on SPI1 (GPIO40-42), UART0 on GPIO44-45, ADC monitors on GPIO46-47, GPIO43 spare.'
              ' Coin door, status LED and GI_SPARE moved onto the switch chain.')
open(F, 'w').write(s)
print('mcu: removed', len(drop), 'items, added', len(add))

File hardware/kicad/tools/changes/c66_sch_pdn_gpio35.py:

"""c66 (schematic): AMP_PDN also driven by the RP2354B (Vincent's card, 2026-11-12: I2C + PDN, 3 wires).

A clean corridor exists from U4 pin 44 (GPIO35): F stub to a via east of the pin, In2 under slow lines only, then
B / F to the AMP_PDN via (c66b board). LINE_DET stays on the 74HC157 only.
- mcu sheet: U4 pin 44 (GPIO35) no-connect -> AMP_PDN.
- audio sheet: R190 10k pull-up kept (amplifiers leave shutdown by themselves while GPIO35 is an input); C158 becomes
  100 nF (1 ms) so the GPIO drives a small load. Firmware: GPIO35 low = shutdown / hard reset, input = run.
Usage: c66_sch_pdn_gpio35.py project_dir"""
import os, re, sys
src = open(os.path.join(os.path.dirname(os.path.abspath(__file__)), 'c62_sch_audio_tas5805m.py')).read()
exec(src[:src.index('# capacitor references')])     # helpers only

p = os.path.join(d, 'mcu.kicad_sch'); s = open(p).read()
m = re.search(r'\n\t\(no_connect\n\t\t\(at 208.28 187.96\)', s); assert m
s = s[:m.start()] + s[block(s, m.start() + 2):]
add = wire((208.28, 187.96), (213.36, 187.96)) + glabel('AMP_PDN', 213.36, 187.96, 0, 'output')
k = s.rstrip().rindex('\n)') + 1
s = s[:k] + add + s[k:]
open(p, 'w').write(s)

p = os.path.join(d, 'audio.kicad_sch'); s = open(p).read()
s = replace_once(s, '(text "Amplifier control: RP2354B I2C1 (GPIO38 SDA / GPIO39 SCL), PDN by RC"',
                 '(text "Amplifier control: RP2354B I2C1 (GPIO38 SDA / GPIO39 SCL), PDN (GPIO35 + RC)"')
s = replace_once(s, '(text "AMP_PDN rises 10 ms after +3V3 (10k / 1 uF). The RP2354B resets both amplifiers\\nover I2C (0x01),',
                 '(text "AMP_PDN rises 1 ms after +3V3 (10k / 100 nF) while GPIO35 is an input. GPIO35 low = hard reset /\\nshutdown; the RP2354B also resets over I2C (0x01),')
i = s.index('(property "Reference" "C158"'); j = s.rindex('\n\t(symbol', 0, i); e = block(s, j + 2)
r = s[j:e]
r = replace_once(r, '(property "Value" "1uF"', '(property "Value" "100nF"')
r = replace_once(r, '"%s"' % D_1U, '"%s"' % D_100N)
s = s[:j] + r + s[e:]
open(p, 'w').write(s)
print('ok')
